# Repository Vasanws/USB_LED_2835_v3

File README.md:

# USB_LED_2835_v3 
A prototype design to accommodate a large scale of LEDs in a single board. A single layout has been duplicate into multiple layout and form into one layout.  
The image below shows the fabricated of the layout on the PCB.

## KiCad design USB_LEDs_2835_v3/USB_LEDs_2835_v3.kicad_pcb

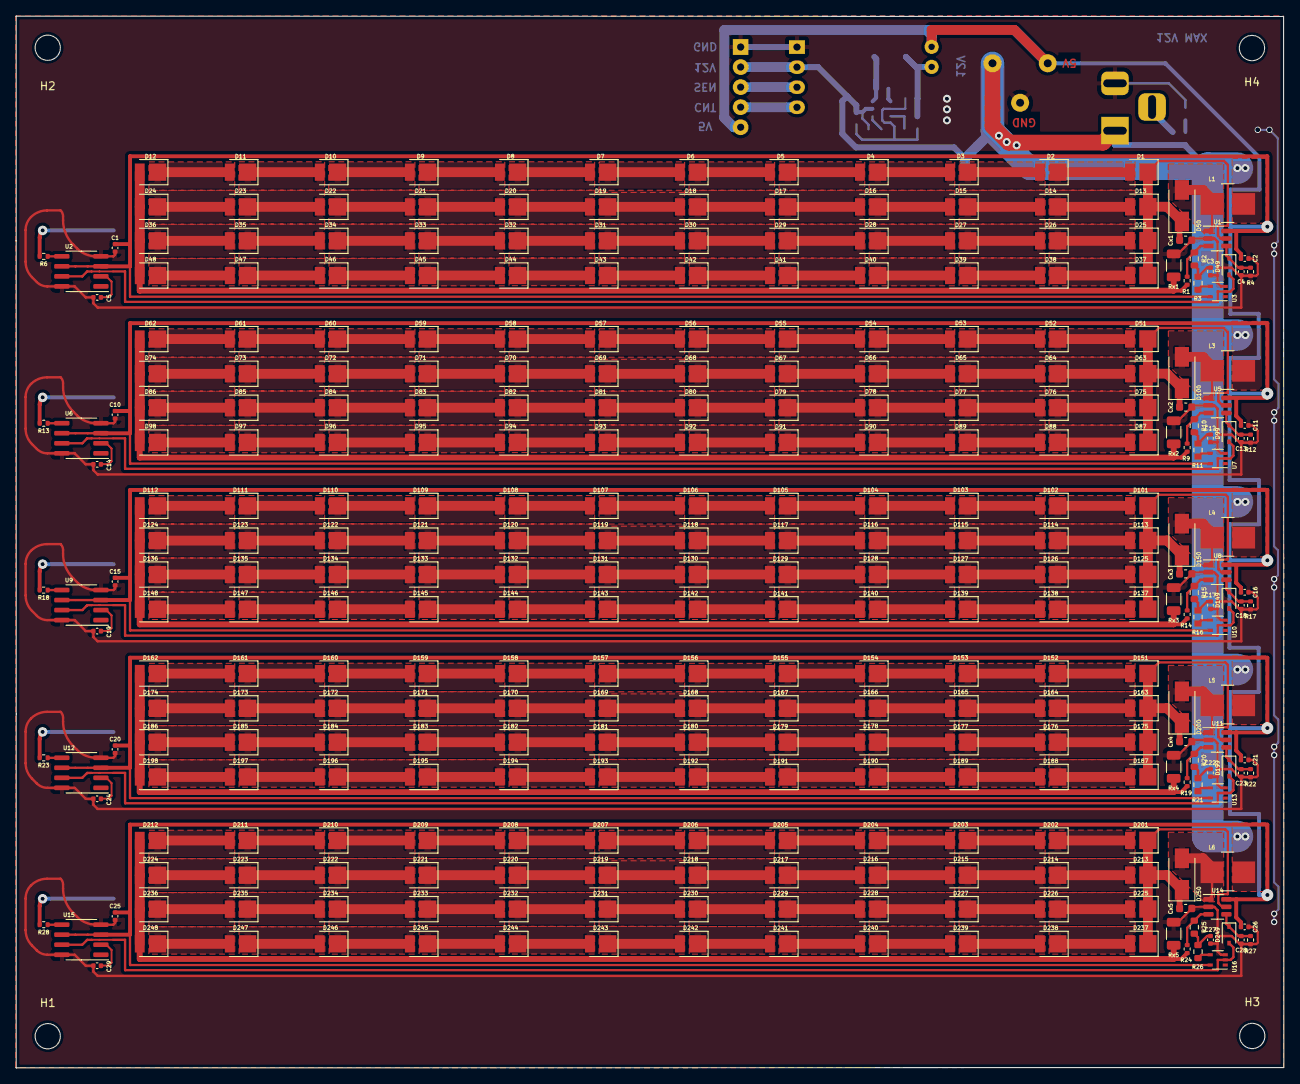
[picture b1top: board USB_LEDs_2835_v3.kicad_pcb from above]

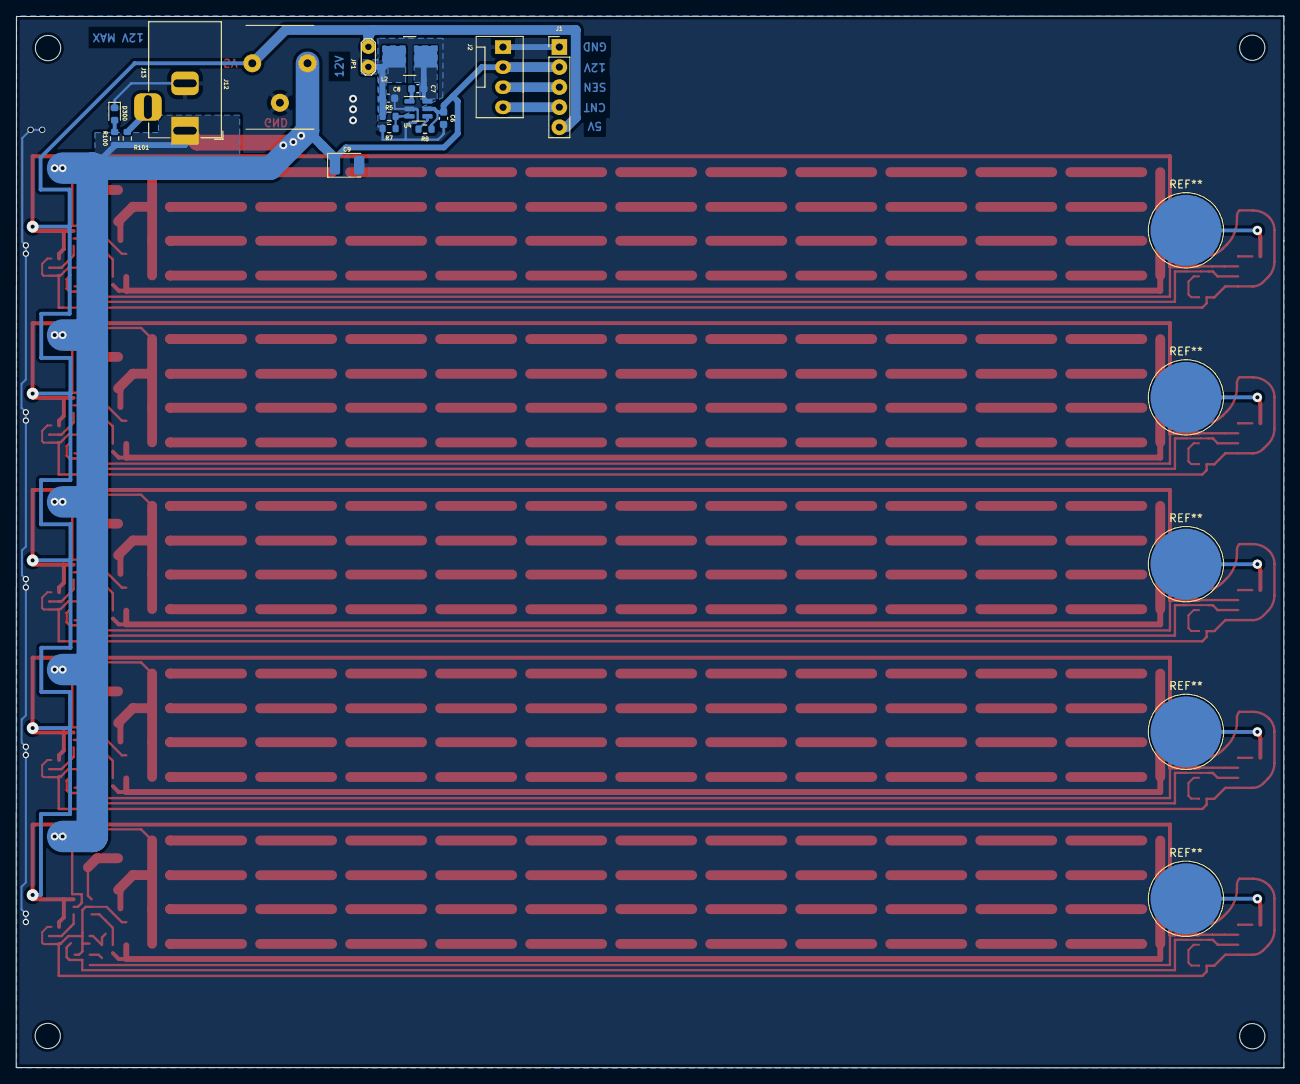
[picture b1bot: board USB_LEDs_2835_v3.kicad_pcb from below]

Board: 2 copper layers, 160.6 x 133.3 mm, 351 parts (17 on the bottom side), 67 nets.

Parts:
C1, C3, C10, C12, C15, C17, C20, C22, C25, C27: 1u; C_0402_1005Metric
C2, C11, C16, C21, C26: 22u; C_0402_1005Metric
C4, C13, C18, C23, C28: 1n; C_0402_1005Metric
C5, C14, C19, C24, C29: 10n; C_0402_1005Metric
C6, C8: 22u; C_0603_1608Metric
C7: 200n; C_0603_1608Metric
C9: 100u/16V; CP_EIA-3528-21_Kemet-B
Cx1, Cx2, Cx3, Cx4, Cx5: 22u; C_0603_1608Metric
D1, D2, D3, D4, D5, D6, D7, D8, D9, D10, D11, D12, D13, D14, D15, D16, D17, D18, D19, D20, D21, D22, D23, D24, D25, D26, D27, D28, D29, D30, D31, D32, D33, D34, D35, D36, D37, D38, D39, D40, D41, D42, D43, D44, D45, D46, D47, D48, D51, D52, D53, D54, D55, D56, D57, D58, D59, D60, D61, D62, D63, D64, D65, D66, D67, D68, D69, D70, D71, D72, D73, D74, D75, D76, D77, D78, D79, D80, D81, D82, D83, D84, D85, D86, D87, D88, D89, D90, D91, D92, D93, D94, D95, D96, D97, D98, D101, D102, D103, D104, D105, D106, D107, D108, D109, D110, D111, D112, D113, D114, D115, D116, D117, D118, D119, D120, D121, D122, D123, D124, D125, D126, D127, D128, D129, D130, D131, D132, D133, D134, D135, D136, D137, D138, D139, D140, D141, D142, D143, D144, D145, D146, D147, D148, D151, D152, D153, D154, D155, D156, D157, D158, D159, D160, D161, D162, D163, D164, D165, D166, D167, D168, D169, D170, D171, D172, D173, D174, D175, D176, D177, D178, D179, D180, D181, D182, D183, D184, D185, D186, D187, D188, D189, D190, D191, D192, D193, D194, D195, D196, D197, D198, D201, D202, D203, D204, D205, D206, D207, D208, D209, D210, D211, D212, D213, D214, D215, D216, D217, D218, D219, D220, D221, D222, D223, D224, D225, D226, D227, D228, D229, D230, D231, D232, D233, D234, D235, D236, D237, D238, D239, D240, D241, D242, D243, D244, D245, D246, D247, D248: 660nm; LED_2835
D49, D99, D149, D199, D249: 1N4148WS; D_SOD-323
D50, D100, D150, D200, D250: SS14; D_SMA
D300: 660nm; LED_0603_1608Metric
H1, H2, H3, H4: MountingHole; MountingHole_3.2mm_M3
J1: external header; PinHeader_1x05_P2.54mm_Vertical
J2: Fan conn; FanPinHeader_1x04_P2.54mm_Vertical_custom
J12: Screw_Terminal_01x03; TerminalBlock_DG250
J13: Barrel_Jack_Switch; BarrelJack_Horizontal
JP1: j_open; TestPoint_2Pads_Pitch2.54mm_Drill0.8mm
L1, L3, L4, L5, L6: L_Ferrite_Small; L_0530_custom
L2: 4.7u; L_0530_custom
R1, R6, R9, R13, R14, R18, R19, R23, R24, R28: 5k; R_0402_1005Metric
R2, R3, R10, R11, R15, R16, R20, R21, R25, R26: 10k; R_0603_1608Metric
R4, R12, R17, R22, R27: 100k; R_0402_1005Metric
R5: 51k; R_0603_1608Metric
R7: 6.8k; R_0603_1608Metric
R8: 22k; R_0603_1608Metric
R100: 2.5k; R_0603_1608Metric
R101: 100k; R_0603_1608Metric
Rx1, Rx2, Rx3, Rx4, Rx5: 100m; R_1206_3216Metric
U1, U5, U8, U11, U14: MT9284; SOT-23-6
U2, U6, U9, U12, U15: JL8022W-L; SOIC-8_3.9x4.9mm_P1.27mm
U3, U7, U10, U13, U16: 74LVC1G04; SOT-353_SC-70-5
U4: STI3470; SOT-23-6

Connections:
+5V: C1.2, C2.1, C10.2, C11.1, C15.2, C16.1, C20.2, C21.1, C25.2, C26.1, J1.5, J12.2, JP1.2 (B), U1.6 (VIN), U2.3 (VDD), U2.6 (OPT1), U3.5 (VCC), U5.6 (VIN), U6.3 (VDD), U6.6 (OPT1), U7.5 (VCC), U8.6 (VIN), U9.3 (VDD), U9.6 (OPT1), U10.5 (VCC), U11.6 (VIN), U12.3 (VDD), U12.6 (OPT1), U13.5 (VCC), U14.6 (VIN), U15.3 (VDD), U15.6 (OPT1), U16.5 (VCC)
+12V: C6.1, C9.1, J1.2, J2.2, J12.1, J13.1, L1.1, L3.1, L4.1, L5.1, L6.1, R8.2, R100.2, R101.1, U4.5 (IN)
GND: C1.1, C2.2, C3.2, C4.2, C5.2, C6.2, C8.2, C9.2, C10.1, C11.2, C12.2, C13.2, C14.2, C15.1, C16.2, C17.2, C18.2, C19.2, C20.1, C21.2, C22.2, C23.2, C24.2, C25.1, C26.2, C27.2, C28.2, C29.2, Cx1.2, Cx2.2, Cx3.2, Cx4.2, Cx5.2, D300.1 (K), J1.1, J2.1, J12.3, J13.2, R4.1, R7.1, R12.1, R17.1, R22.1, R27.1, Rx1.1, Rx2.1, Rx3.1, Rx4.1, Rx5.1, U1.2 (GND), U2.4 (GND), U2.8 (OPT2), U3.3 (GND), U4.2 (GND), U5.2 (GND), U6.4 (GND), U6.8 (OPT2), U7.3 (GND), U8.2 (GND), U9.4 (GND), U9.8 (OPT2), U10.3 (GND), U11.2 (GND), U12.4 (GND), U12.8 (OPT2), U13.3 (GND), U14.2 (GND), U15.4 (GND), U15.8 (OPT2), U16.3 (GND)
unnamed: C3.1, C12.1, C17.1, C22.1, C27.1, R2.2, R3.2, R10.2, R11.2, R15.2, R16.2, R20.2, R21.2, R25.2, R26.2
unnamed: C4.1, C13.1, C18.1, C23.1, C28.1, D49.1 (K), D99.1 (K), D149.1 (K), D199.1 (K), D249.1 (K), R4.2, R12.2, R17.2, R22.2, R27.2, U1.4 (EN), U5.4 (EN), U8.4 (EN), U11.4 (EN), U14.4 (EN)
unnamed: C5.1, C14.1, C19.1, C24.1, C29.1, U2.2 (VC), U6.2 (VC), U9.2 (VC), U12.2 (VC), U15.2 (VC)
unnamed: C7.1, U4.1 (BS)
unnamed: C7.2, L2.1, U4.6 (LX)
unnamed: C8.1, JP1.1 (A), L2.2, R5.1
unnamed: Cx1.1, Cx2.1, Cx3.1, Cx4.1, Cx5.1, D1.2 (A), D13.2 (A), D25.2 (A), D37.2 (A), D50.1 (K), D51.2 (A), D63.2 (A), D75.2 (A), D87.2 (A), D100.1 (K), D101.2 (A), D113.2 (A), D125.2 (A), D137.2 (A), D150.1 (K), D151.2 (A), D163.2 (A), D175.2 (A), D187.2 (A), D200.1 (K), D201.2 (A), D213.2 (A), D225.2 (A), D237.2 (A), D250.1 (K), U1.5 (OV), U5.5 (OV), U8.5 (OV), U11.5 (OV), U14.5 (OV)
unnamed: D1.1 (K), D2.2 (A), D51.1 (K), D52.2 (A), D101.1 (K), D102.2 (A), D151.1 (K), D152.2 (A), D201.1 (K), D202.2 (A)
unnamed: D2.1 (K), D3.2 (A), D52.1 (K), D53.2 (A), D102.1 (K), D103.2 (A), D152.1 (K), D153.2 (A), D202.1 (K), D203.2 (A)
unnamed: D3.1 (K), D4.2 (A), D53.1 (K), D54.2 (A), D103.1 (K), D104.2 (A), D153.1 (K), D154.2 (A), D203.1 (K), D204.2 (A)
unnamed: D4.1 (K), D5.2 (A), D54.1 (K), D55.2 (A), D104.1 (K), D105.2 (A), D154.1 (K), D155.2 (A), D204.1 (K), D205.2 (A)
unnamed: D5.1 (K), D6.2 (A), D55.1 (K), D56.2 (A), D105.1 (K), D106.2 (A), D155.1 (K), D156.2 (A), D205.1 (K), D206.2 (A)
unnamed: D6.1 (K), D7.2 (A), D56.1 (K), D57.2 (A), D106.1 (K), D107.2 (A), D156.1 (K), D157.2 (A), D206.1 (K), D207.2 (A)
unnamed: D7.1 (K), D8.2 (A), D57.1 (K), D58.2 (A), D107.1 (K), D108.2 (A), D157.1 (K), D158.2 (A), D207.1 (K), D208.2 (A)
unnamed: D8.1 (K), D9.2 (A), D58.1 (K), D59.2 (A), D108.1 (K), D109.2 (A), D158.1 (K), D159.2 (A), D208.1 (K), D209.2 (A)
unnamed: D10.1 (K), D11.2 (A), D60.1 (K), D61.2 (A), D110.1 (K), D111.2 (A), D160.1 (K), D161.2 (A), D210.1 (K), D211.2 (A)
unnamed: D9.1 (K), D10.2 (A), D59.1 (K), D60.2 (A), D109.1 (K), D110.2 (A), D159.1 (K), D160.2 (A), D209.1 (K), D210.2 (A)
unnamed: D11.1 (K), D12.2 (A), D61.1 (K), D62.2 (A), D111.1 (K), D112.2 (A), D161.1 (K), D162.2 (A), D211.1 (K), D212.2 (A)
unnamed: D12.1 (K), D24.1 (K), D36.1 (K), D48.1 (K), D62.1 (K), D74.1 (K), D86.1 (K), D98.1 (K), D112.1 (K), D124.1 (K), D136.1 (K), D148.1 (K), D162.1 (K), D174.1 (K), D186.1 (K), D198.1 (K), D212.1 (K), D224.1 (K), D236.1 (K), D248.1 (K), R1.1, R9.1, R14.1, R19.1, R24.1, Rx1.2, Rx2.2, Rx3.2, Rx4.2, Rx5.2
unnamed: D13.1 (K), D14.2 (A), D63.1 (K), D64.2 (A), D113.1 (K), D114.2 (A), D163.1 (K), D164.2 (A), D213.1 (K), D214.2 (A)
unnamed: D14.1 (K), D15.2 (A), D64.1 (K), D65.2 (A), D114.1 (K), D115.2 (A), D164.1 (K), D165.2 (A), D214.1 (K), D215.2 (A)
unnamed: D15.1 (K), D16.2 (A), D65.1 (K), D66.2 (A), D115.1 (K), D116.2 (A), D165.1 (K), D166.2 (A), D215.1 (K), D216.2 (A)
unnamed: D16.1 (K), D17.2 (A), D66.1 (K), D67.2 (A), D116.1 (K), D117.2 (A), D166.1 (K), D167.2 (A), D216.1 (K), D217.2 (A)
unnamed: D17.1 (K), D18.2 (A), D67.1 (K), D68.2 (A), D117.1 (K), D118.2 (A), D167.1 (K), D168.2 (A), D217.1 (K), D218.2 (A)
unnamed: D18.1 (K), D19.2 (A), D68.1 (K), D69.2 (A), D118.1 (K), D119.2 (A), D168.1 (K), D169.2 (A), D218.1 (K), D219.2 (A)
unnamed: D19.1 (K), D20.2 (A), D69.1 (K), D70.2 (A), D119.1 (K), D120.2 (A), D169.1 (K), D170.2 (A), D219.1 (K), D220.2 (A)
unnamed: D20.1 (K), D21.2 (A), D70.1 (K), D71.2 (A), D120.1 (K), D121.2 (A), D170.1 (K), D171.2 (A), D220.1 (K), D221.2 (A)
unnamed: D21.1 (K), D22.2 (A), D71.1 (K), D72.2 (A), D121.1 (K), D122.2 (A), D171.1 (K), D172.2 (A), D221.1 (K), D222.2 (A)
unnamed: D22.1 (K), D23.2 (A), D72.1 (K), D73.2 (A), D122.1 (K), D123.2 (A), D172.1 (K), D173.2 (A), D222.1 (K), D223.2 (A)
unnamed: D23.1 (K), D24.2 (A), D73.1 (K), D74.2 (A), D123.1 (K), D124.2 (A), D173.1 (K), D174.2 (A), D223.1 (K), D224.2 (A)
unnamed: D25.1 (K), D26.2 (A), D75.1 (K), D76.2 (A), D125.1 (K), D126.2 (A), D175.1 (K), D176.2 (A), D225.1 (K), D226.2 (A)
unnamed: D26.1 (K), D27.2 (A), D76.1 (K), D77.2 (A), D126.1 (K), D127.2 (A), D176.1 (K), D177.2 (A), D226.1 (K), D227.2 (A)
unnamed: D27.1 (K), D28.2 (A), D77.1 (K), D78.2 (A), D127.1 (K), D128.2 (A), D177.1 (K), D178.2 (A), D227.1 (K), D228.2 (A)
unnamed: D28.1 (K), D29.2 (A), D78.1 (K), D79.2 (A), D128.1 (K), D129.2 (A), D178.1 (K), D179.2 (A), D228.1 (K), D229.2 (A)
unnamed: D29.1 (K), D30.2 (A), D79.1 (K), D80.2 (A), D129.1 (K), D130.2 (A), D179.1 (K), D180.2 (A), D229.1 (K), D230.2 (A)
unnamed: D30.1 (K), D31.2 (A), D80.1 (K), D81.2 (A), D130.1 (K), D131.2 (A), D180.1 (K), D181.2 (A), D230.1 (K), D231.2 (A)
unnamed: D31.1 (K), D32.2 (A), D81.1 (K), D82.2 (A), D131.1 (K), D132.2 (A), D181.1 (K), D182.2 (A), D231.1 (K), D232.2 (A)
unnamed: D32.1 (K), D33.2 (A), D82.1 (K), D83.2 (A), D132.1 (K), D133.2 (A), D182.1 (K), D183.2 (A), D232.1 (K), D233.2 (A)
unnamed: D33.1 (K), D34.2 (A), D83.1 (K), D84.2 (A), D133.1 (K), D134.2 (A), D183.1 (K), D184.2 (A), D233.1 (K), D234.2 (A)
unnamed: D34.1 (K), D35.2 (A), D84.1 (K), D85.2 (A), D134.1 (K), D135.2 (A), D184.1 (K), D185.2 (A), D234.1 (K), D235.2 (A)
unnamed: D35.1 (K), D36.2 (A), D85.1 (K), D86.2 (A), D135.1 (K), D136.2 (A), D185.1 (K), D186.2 (A), D235.1 (K), D236.2 (A)
unnamed: D37.1 (K), D38.2 (A), D87.1 (K), D88.2 (A), D137.1 (K), D138.2 (A), D187.1 (K), D188.2 (A), D237.1 (K), D238.2 (A)
unnamed: D38.1 (K), D39.2 (A), D88.1 (K), D89.2 (A), D138.1 (K), D139.2 (A), D188.1 (K), D189.2 (A), D238.1 (K), D239.2 (A)
unnamed: D39.1 (K), D40.2 (A), D89.1 (K), D90.2 (A), D139.1 (K), D140.2 (A), D189.1 (K), D190.2 (A), D239.1 (K), D240.2 (A)
unnamed: D40.1 (K), D41.2 (A), D90.1 (K), D91.2 (A), D140.1 (K), D141.2 (A), D190.1 (K), D191.2 (A), D240.1 (K), D241.2 (A)
unnamed: D41.1 (K), D42.2 (A), D91.1 (K), D92.2 (A), D141.1 (K), D142.2 (A), D191.1 (K), D192.2 (A), D241.1 (K), D242.2 (A)
unnamed: D42.1 (K), D43.2 (A), D92.1 (K), D93.2 (A), D142.1 (K), D143.2 (A), D192.1 (K), D193.2 (A), D242.1 (K), D243.2 (A)
unnamed: D43.1 (K), D44.2 (A), D93.1 (K), D94.2 (A), D143.1 (K), D144.2 (A), D193.1 (K), D194.2 (A), D243.1 (K), D244.2 (A)
unnamed: D44.1 (K), D45.2 (A), D94.1 (K), D95.2 (A), D144.1 (K), D145.2 (A), D194.1 (K), D195.2 (A), D244.1 (K), D245.2 (A)
unnamed: D45.1 (K), D46.2 (A), D95.1 (K), D96.2 (A), D145.1 (K), D146.2 (A), D195.1 (K), D196.2 (A), D245.1 (K), D246.2 (A)
unnamed: D46.1 (K), D47.2 (A), D96.1 (K), D97.2 (A), D146.1 (K), D147.2 (A), D196.1 (K), D197.2 (A), D246.1 (K), D247.2 (A)
unnamed: D47.1 (K), D48.2 (A), D97.1 (K), D98.2 (A), D147.1 (K), D148.2 (A), D197.1 (K), D198.2 (A), D247.1 (K), D248.2 (A)
unnamed: D49.2 (A), D99.2 (A), D149.2 (A), D199.2 (A), D249.2 (A), U2.7 (SO), U3.2, U6.7 (SO), U7.2, U9.7 (SO), U10.2, U12.7 (SO), U13.2, U15.7 (SO), U16.2
unnamed: D50.2 (A), D100.2 (A), D150.2 (A), D200.2 (A), D250.2 (A), L1.2, L3.2, L4.2, L5.2, L6.2, U1.1 (SW), U5.1 (SW), U8.1 (SW), U11.1 (SW), U14.1 (SW)
unnamed: D300.2 (A), R100.1
unnamed: J1.3, J2.3
unnamed: J1.4, J2.4
unnamed: J13.3, R101.2
unnamed: R1.2, R2.1, R9.2, R10.1, R14.2, R15.1, R19.2, R20.1, R24.2, R25.1, U1.3 (FB), U5.3 (FB), U8.3 (FB), U11.3 (FB), U14.3 (FB)
unnamed: R3.1, R11.1, R16.1, R21.1, R26.1, U3.4, U7.4, U10.4, U13.4, U16.4
unnamed: R5.2, R7.2, U4.3 (FB)
unnamed: R6.1, R13.1, R18.1, R23.1, R28.1
unnamed: R6.2, R13.2, R18.2, R23.2, R28.2, U2.5 (TI), U6.5 (TI), U9.5 (TI), U12.5 (TI), U15.5 (TI)
unnamed: R8.1, U4.4 (EN)
